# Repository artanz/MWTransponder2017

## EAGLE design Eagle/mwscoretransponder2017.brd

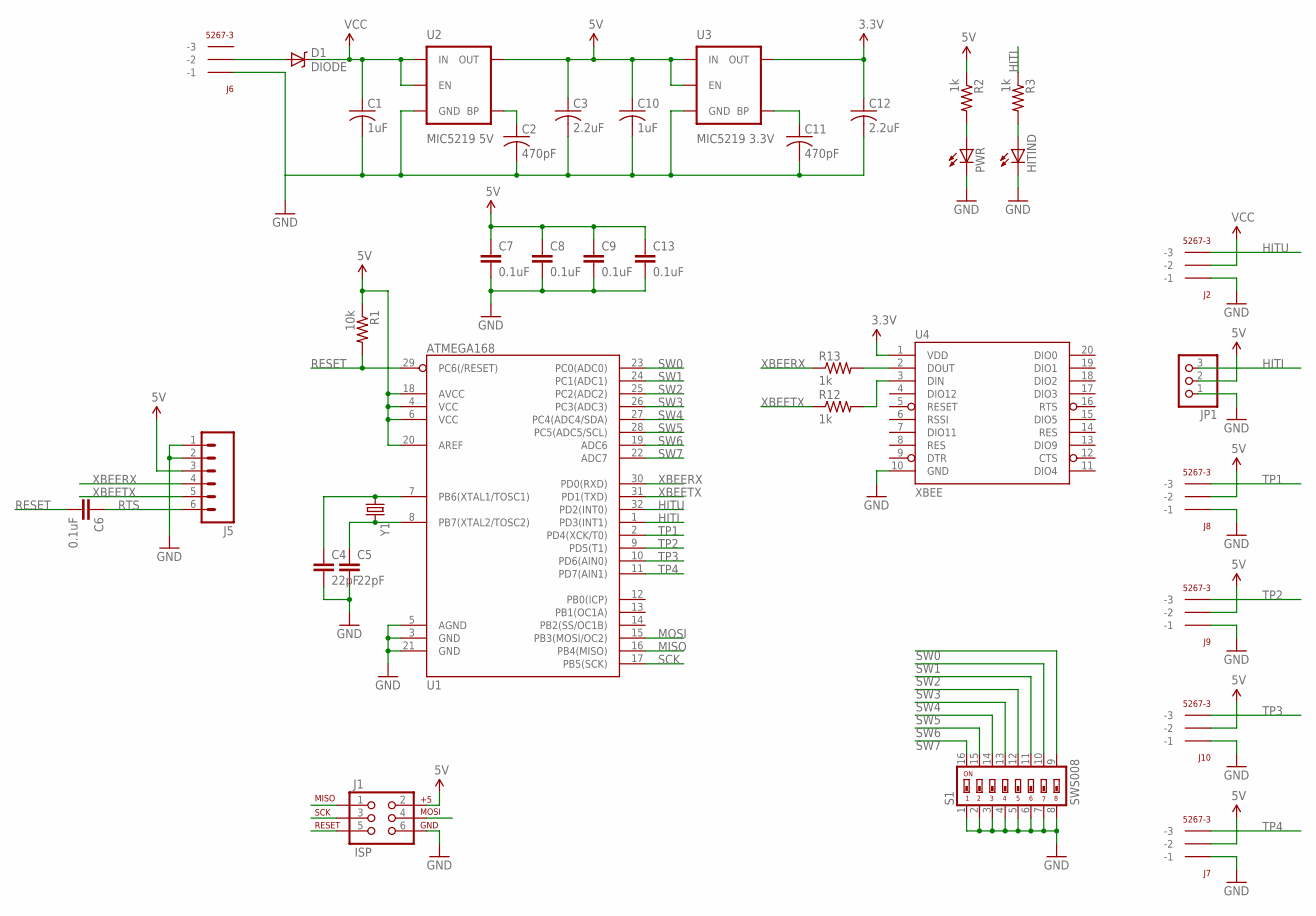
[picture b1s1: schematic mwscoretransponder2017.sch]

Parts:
C1, C10: 1uF; C0603
C2, C11: 470pF; C0603
C3, C12: 2.2uF; C0805
C4, C5: 22pF; 0603-CAP
C6, C7, C8, C9, C13: 0.1uF; 0603-CAP
D1: DIODE; SMA-DIODE
HITIND: LED0603; LED-0603
J1: ISP; 2X3
J2, J6, J7, J8, J9, J10: 5267-3
J5: M06SIP; 1X06
JP1: PINHD-1X3; 1X03
PWR: LED0603; LED-0603
R1: 10k; 0603-RES
R2, R3, R12, R13: 1k; 0603-RES
S1: SWS008; SMS-008
U1: ATMEGA168; TQFP32-08
U2: MIC5219 5V; SOT23-5
U3: MIC5219 3.3V; SOT23-5
U4: XBEE; XBEE-SMD
Y1: CRYSTAL5X3; CRYSTAL-SMD-5X3

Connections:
3.3V: C12.1, U3.5 (OUT), U4.1 (VDD)
5V: C3.1, C7.1, C8.1, C9.1, C10.1, C13.1, J1.2, J5.3, J7.P$2 (-2), J8.P$2 (-2), J9.P$2 (-2), J10.P$2 (-2), JP1.2, R1.1, R2.1, U1.4 (VCC), U1.6 (VCC), U1.18 (AVCC), U1.20 (AREF), U2.5 (OUT), U3.1 (IN), U3.3 (EN)
GND: C1.2, C2.2, C3.2, C4.2, C5.2, C7.2, C8.2, C9.2, C10.2, C11.2, C12.2, C13.2, HITIND.C, J1.6, J2.P$1 (-1), J5.1, J5.2, J6.P$1 (-1), J7.P$1 (-1), J8.P$1 (-1), J9.P$1 (-1), J10.P$1 (-1), JP1.1, PWR.C, S1.1, S1.2, S1.3, S1.4, S1.5, S1.6, S1.7, S1.8, U1.3 (GND), U1.5 (AGND), U1.21 (GND), U2.2 (GND), U3.2 (GND), U4.10 (GND)
HITI: JP1.3, R3.1, U1.1 (PD3(INT1))
HITU: J2.P$3 (-3), U1.32 (PD2(INT0))
MISO: J1.1, U1.16 (PB4(MISO))
MOSI: J1.4, U1.15 (PB3(MOSI/OC2))
unnamed: PWR.A, R2.2
unnamed: HITIND.A, R3.2
unnamed: C4.1, U1.7 (PB6(XTAL1/TOSC1)), Y1.1
unnamed: D1.A, J6.P$2 (-2)
unnamed: C5.1, U1.8 (PB7(XTAL2/TOSC2)), Y1.3 (2)
unnamed: R13.2, U4.2 (DOUT)
unnamed: R12.2, U4.3 (DIN)
unnamed: C11.1, U3.4 (BP)
unnamed: C2.1, U2.4 (BP)
RESET: C6.2, J1.5, R1.2, U1.29 (PC6(/RESET))
RTS: C6.1, J5.6
SCK: J1.3, U1.17 (PB5(SCK))
SW0: S1.9, U1.23 (PC0(ADC0))
SW1: S1.10, U1.24 (PC1(ADC1))
SW2: S1.11, U1.25 (PC2(ADC2))
SW3: S1.12, U1.26 (PC3(ADC3))
SW4: S1.13, U1.27 (PC4(ADC4/SDA))
SW5: S1.14, U1.28 (PC5(ADC5/SCL))
SW6: S1.15, U1.19 (ADC6)
SW7: S1.16, U1.22 (ADC7)
TP1: J8.P$3 (-3), U1.2 (PD4(XCK/T0))
TP2: J9.P$3 (-3), U1.9 (PD5(T1))
TP3: J10.P$3 (-3), U1.10 (PD6(AIN0))
TP4: J7.P$3 (-3), U1.11 (PD7(AIN1))
VCC: C1.1, D1.C, J2.P$2 (-2), U2.1 (IN), U2.3 (EN)
XBEERX: J5.4, R13.1, U1.30 (PD0(RXD))
XBEETX: J5.5, R12.1, U1.31 (PD1(TXD))

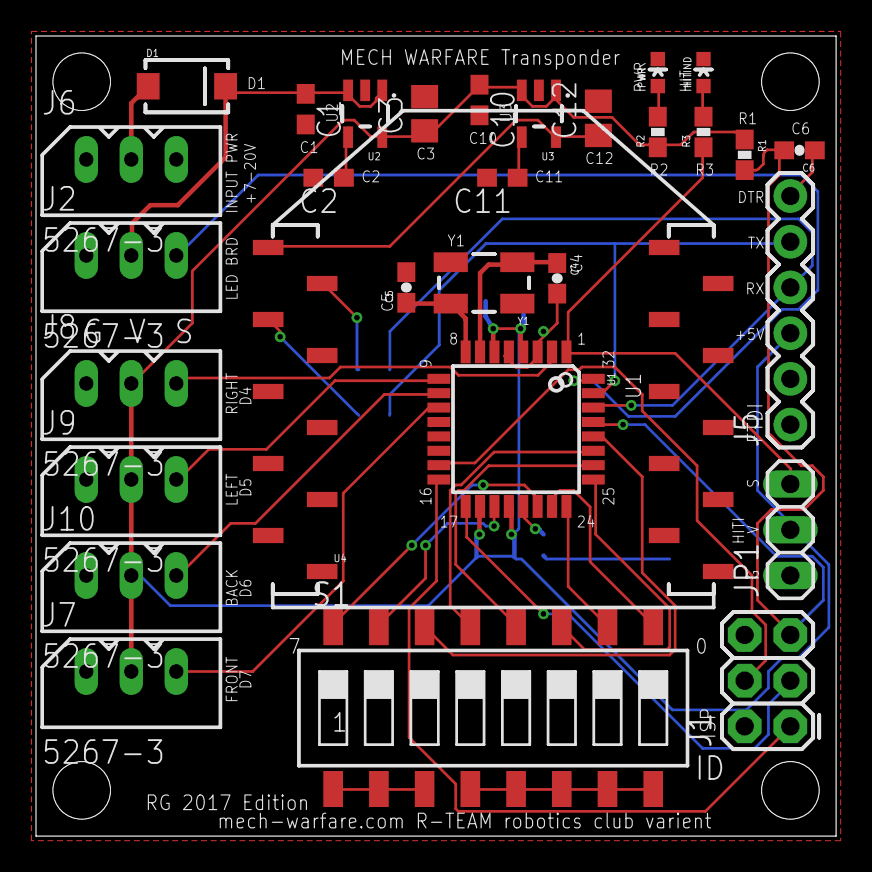
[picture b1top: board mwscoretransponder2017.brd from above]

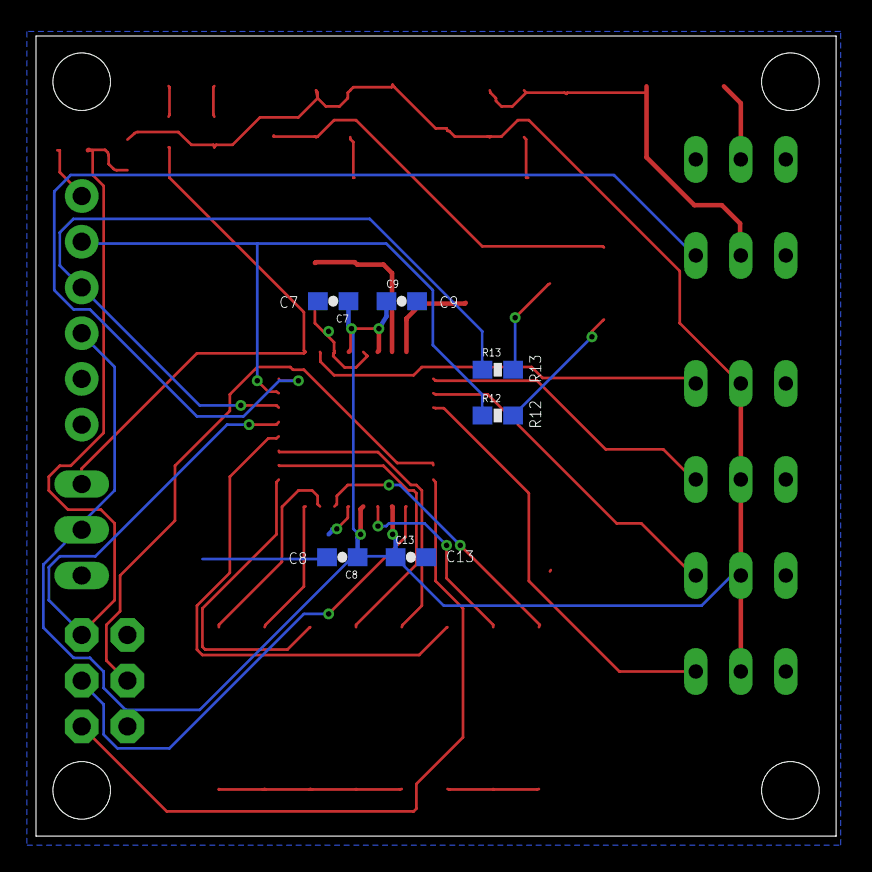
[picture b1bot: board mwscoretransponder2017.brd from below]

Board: 2 copper layers, 44.5 x 44.5 mm, 36 parts (6 on the bottom side), 34 nets.

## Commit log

2017-03-02 :space_invader: Added .gitattributes & .gitignore files
2017-03-02 Initial Commit
    Initial Commit
2017-03-03 Minor Updates
    Minor Updates

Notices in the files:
parts and their libraries:
SparkFun: Licensing: CC v3.0 Share-Alike You are welcome to use this library for commercial purposes.
SparkFun-PowerIC: Licensing: Creative Commons ShareAlike 4.0 International - https://creativecommons.org/licenses/by-sa/4.0
